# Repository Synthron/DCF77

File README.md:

# DCF77

DCF77-Clock with Multi-LED display with STM32

---

## Decription

This DCF77 Clock not only displays the time and date, but also analyzes and visualizes the signal received.  
The LED rings are placed as such that each LED is on its respective position on a standard clock face.  
The 7 Segment Displays show the time and date in a more readable format.

### Inner LED Ring

The inner LED ring clocks in the data for the current minute telegram. Each "1"-bit will be displayed by the LED lit up, on a "0", the LED is off respectively.

### Outer LED Ring

The outer LED ring gets updated after the current minute data is complete. On the "0-Second"-Mark, the data from the inner ring gets pushed to the outer ring and analyzed. The resulting data will then be displayed on the 7-Segment-Displays as well as the status LEDs. Also at each full hour, the internal RTC gets updated.

### RTC behaviour

1. Initial startup  
After the initial power-up the current RTC value will be pushed to the displays. This time information can only be trusted, once the module has received a valid telegram and was not powered down for more than 3 days.  
2. First received data  
Once the first valid data was received, it will be pushed into the RTC to update it. After successful write, the RTC_LOCK-LED will be on to indicate trustful data stored in the RTC.  
3. On the hour  
To mitigate possible clock drift, the RTC will be updated on the full hour. This ensures up-to-date data stored in it.

---

## Roadmap Hardware

- [x] finalize schematic
- [x] Set footprints
- [x] decide LED layout
  - all on one board
  - ~~seperate frontpanel pcb~~
- [x] Draw Layout
- [x] Review by theBrutzler
- [x] Order Parts
- [x] check footprints
- [x] Order PCB
- [x] Assemble

---

## Roadmap Software

- [ ] get USB running (for Debug)
- [x] Get DCF77 Antenna working and bits decoded
- [x] get MCP7221 running
- [x] get shift registers running
- [x] set up flags for stats and data
- [x] get LED rings running
- [x] get RTC running
- [x] Sync everything to start of minute/second
- [ ] get everything running together

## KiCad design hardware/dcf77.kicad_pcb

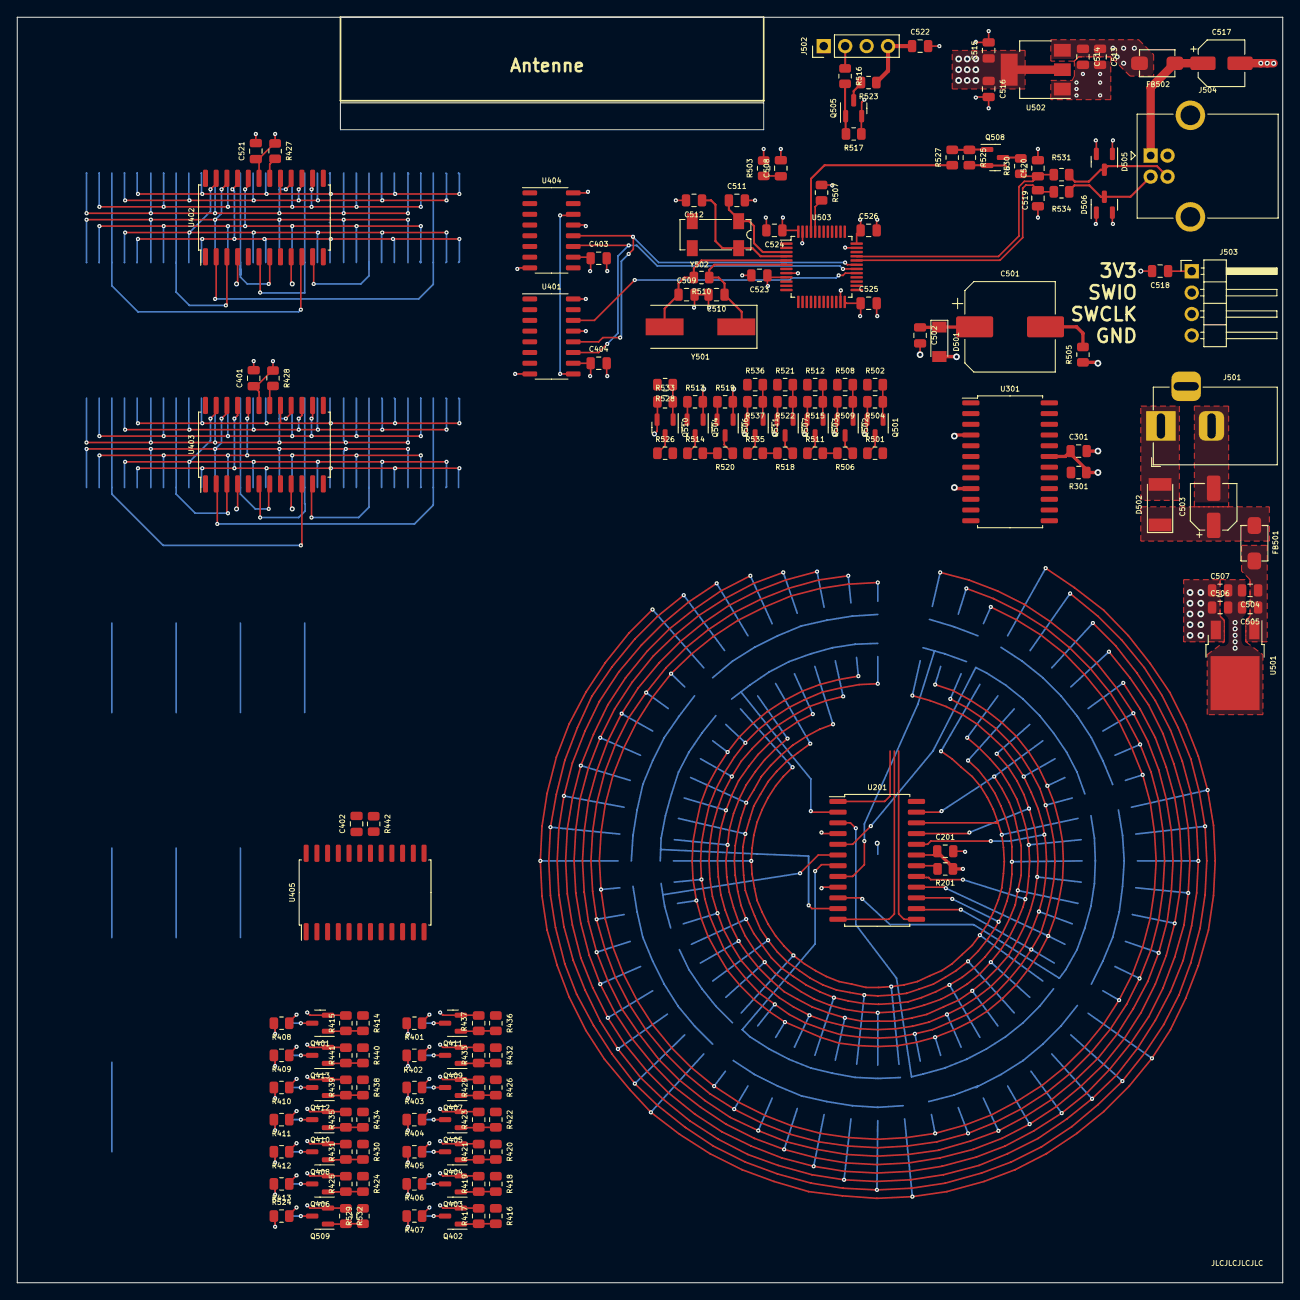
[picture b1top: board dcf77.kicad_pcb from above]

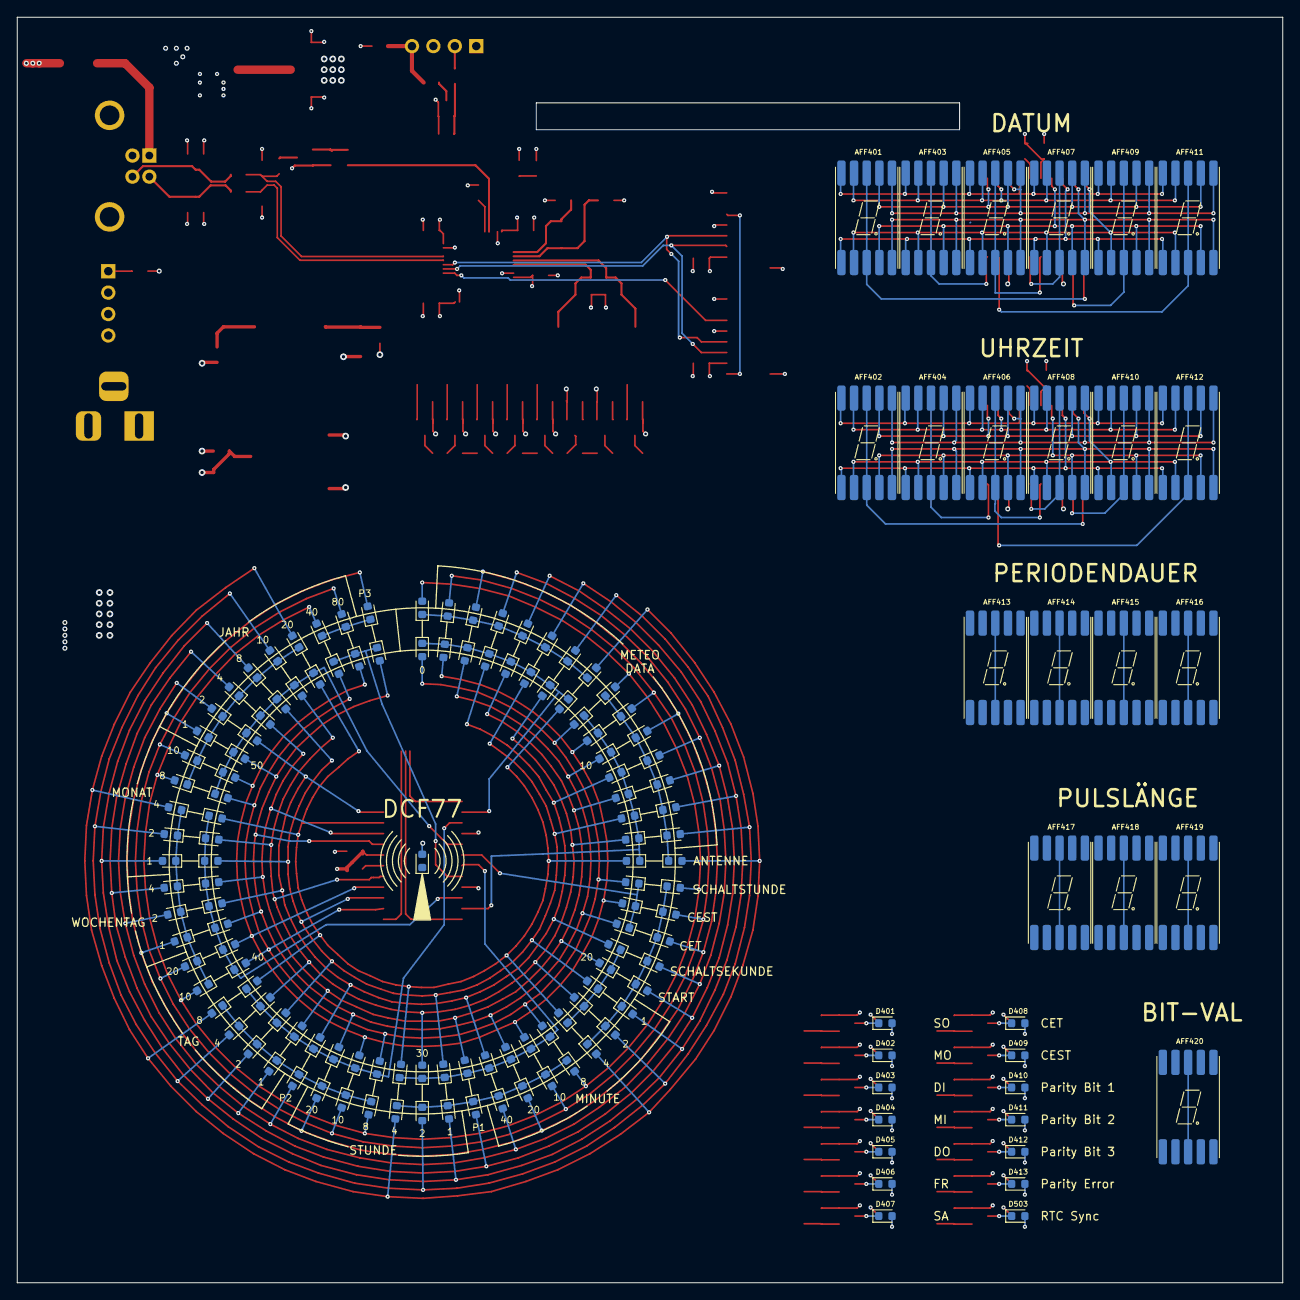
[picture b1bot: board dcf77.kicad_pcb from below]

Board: 4 copper layers, 150.0 x 150.0 mm, 312 parts (153 on the bottom side), 191 nets.

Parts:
AFF401, AFF402, AFF403, AFF404, AFF405, AFF406, AFF407, AFF408, AFF409, AFF410, AFF411, AFF412, AFF413, AFF414, AFF415, AFF416, AFF417, AFF418, AFF419, AFF420: LTS-6980HR; 7_Segment_SMD
C201, C301, C401, C402, C403, C404, C502, C505, C506, C508, C514, C515, C518, C521, C522, C523, C524, C525, C526: 100n; C_0805_2012Metric
C501: 0.22F/5V5; CP_Elec_10x10.5
C503: 100µ; CP_Elec_5x5.8
C504, C507, C513, C516: 1µ; C_0805_2012Metric
C509, C510, C511, C512: 20p; C_0805_2012Metric
C517: 10µ; CP_Elec_5x5.8
C519, C520: 47p; C_0805_2012Metric
D201, D202, D203, D204, D205, D206, D207, D208, D209, D210, D211, D212, D213, D214, D215, D216, D217, D218, D219, D220, D221, D222, D223, D224, D225, D226, D227, D228, D229, D230, D231, D232, D233, D234, D235, D236, D237, D238, D239, D240, D241, D242, D243, D244, D245, D246, D247, D248, D249, D250, D251, D252, D253, D254, D255, D256, D257, D258, D259, D301, D302, D303, D304, D305, D306, D307, D308, D309, D310, D311, D312, D313, D314, D315, D316, D317, D318, D319, D320, D321, D322, D323, D324, D325, D326, D327, D328, D329, D330, D331, D332, D333, D334, D335, D336, D337, D338, D339, D340, D341, D342, D343, D344, D345, D346, D347, D348, D349, D350, D351, D352, D353, D354, D355, D356, D357, D358, D359: LED; LED_0603_1608Metric
D401: Mo; LED_0603_1608Metric
D402: Di; LED_0603_1608Metric
D403: Mi; LED_0603_1608Metric
D404: Do; LED_0603_1608Metric
D405: Fr; LED_0603_1608Metric
D406: Sa; LED_0603_1608Metric
D407: So; LED_0603_1608Metric
D408: CET; LED_0603_1608Metric
D409: CEST; LED_0603_1608Metric
D410: P1; LED_0603_1608Metric
D411: P2; LED_0603_1608Metric
D412: P3; LED_0603_1608Metric
D413: PE; LED_0603_1608Metric
D501: LL4148; D_MiniMELF
D502: SM4007; D_MELF
D503: RTC; LED_0603_1608Metric
D504: SIG; LED_0603_1608Metric
D505, D506: BAV199; SOT-23
FB501, FB502: FerriteBead; SMB-001
J501: Jack-DC; BarrelJack_Horizontal
J502: DCF77 Antenna; PinHeader_1x04_P2.54mm_Vertical
J503: SWD; PinHeader_1x04_P2.54mm_Horizontal
J504: USB_B; USB_B_OST_USB-B1HSxx_Horizontal
Q401, Q402, Q403, Q404, Q405, Q406, Q407, Q408, Q409, Q410, Q411, Q412, Q413, Q501, Q502, Q503, Q504, Q505, Q506, Q507, Q509, Q510, Q511: BSS138; SOT-23
Q508: BC856; SOT-23
R201, R301, R427, R428, R442: 20k; R_0805_2012Metric
R401, R402, R403, R404, R405, R406, R407, R408, R409, R410, R411, R412, R413: R; R_0805_2012Metric
R414, R416, R418, R420, R422, R424, R426, R430, R432, R434, R436, R438, R440, R501, R502, R503, R505, R506, R507, R508, R511, R512, R513, R514, R516, R518, R519, R520, R521, R523, R528, R529, R535, R536: 10k; R_0805_2012Metric
R415, R417, R419, R421, R423, R425, R429, R431, R433, R435, R437, R439, R441, R504, R509, R515, R517, R522, R525, R527, R532, R533, R537: 100k; R_0805_2012Metric
R510: 1M; R_0805_2012Metric
R524, R526: 1k; R_0805_2012Metric
R530: 1k5; R_0805_2012Metric
R531, R534: 22; R_0805_2012Metric
U201, U301, U402, U403, U405: MAX7221xWG; SOIC-24W_7.5x15.4mm_P1.27mm
U401, U404: 74HC595; SO-16_3.9x9.9mm_P1.27mm
U501: L7805; TO-252-2
U502: AZ1117-3.3; SOT-223-3_TabPin2
U503: STM32F103C8Tx; LQFP-48_7x7mm_P0.5mm
Y501: 8MHz; Crystal_SMD_HC49-SD
Y502: 32.768kHz; Crystal_SMD_SeikoEpson_MC306-4Pin_8.0x3.2mm

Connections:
+3V3: C403.1, C404.1, C515.1, C516.1, C518.1, C522.1, C523.1, C524.1, C525.1, C526.1, D501.2 (A), D505.2, D506.2, J502.4, J503.1, Q504.1 (G), Q506.1 (G), Q508.2 (E), R503.2, R513.2, R519.2, R523.1, R525.2, U401.10 (~SRCLR), U401.16 (VCC), U404.10 (~SRCLR), U404.16 (VCC), U502.2 (VO), U503.9 (VDDA), U503.24 (VDD), U503.36 (VDD), U503.48 (VDD)
+5V: C201.1, C301.1, C401.1, C402.1, C506.1, C507.1, C513.1, C514.1, C521.1, D504.2 (A), FB502.2, R201.1, R301.1, R401.1, R402.1, R403.1, R404.1, R405.1, R406.1, R407.1, R408.1, R409.1, R410.1, R411.1, R412.1, R413.1, R427.1, R428.1, R442.1, R501.2, R506.2, R511.2, R514.2, R518.2, R520.2, R524.2, R535.2, U201.19 (V+), U301.19 (V+), U402.19 (V+), U403.19 (V+), U405.19 (V+), U501.3 (OUT), U502.3 (VI)
/CPU/CLK: Q504.3 (D), R514.1, U201.13 (CLK), U301.13 (CLK), U402.13 (CLK), U403.13 (CLK), U405.13 (CLK)
/CPU/MOSI: Q506.3 (D), R520.1, U201.1 (DIN), U301.1 (DIN), U402.1 (DIN), U403.1 (DIN), U405.1 (DIN)
/CPU/SER_CLK: U401.11 (SRCLK), U404.11 (SRCLK), U503.30 (PA9)
/CPU/SER_Data: U401.14 (SER), U503.29 (PA8)
/CPU/SER_Latch: U401.12 (RCLK), U404.12 (RCLK), U503.31 (PA10)
GND: C201.2, C301.2, C401.2, C402.2, C403.2, C404.2, C502.2, C503.2, C504.2, C505.2, C506.2, C507.2, C508.2, C509.2, C510.2, C511.2, C512.2, C513.2, C514.2, C515.2, C516.2, C517.2, C518.2, C519.2, C520.2, C521.2, C522.2, C523.2, C524.2, C525.2, C526.2, D505.1, D506.1, J501.2, J502.3, J503.4, J504.4 (GND), J504.5 (Shield), Q401.2 (S), Q402.2 (S), Q403.2 (S), Q404.2 (S), Q405.2 (S), Q406.2 (S), Q407.2 (S), Q408.2 (S), Q409.2 (S), Q410.2 (S), Q411.2 (S), Q412.2 (S), Q413.2 (S), Q501.2 (S), Q502.2 (S), Q503.2 (S), Q505.2 (S), Q507.2 (S), Q509.2 (S), Q510.2 (S), Q511.2 (S), R415.2, R417.2, R419.2, R421.2, R423.2, R425.2, R429.2, R431.2, R433.2, R435.2, R437.2, R439.2, R441.2, R504.2, R505.1, R507.1, R509.2, R515.2, R517.1, R522.2, R532.1, R533.1, R537.2, U201.4 (GND), U201.9 (GND), U301.4 (GND), U301.9 (GND), U401.8 (GND), U401.13 (~OE), U402.4 (GND), U402.9 (GND), U403.4 (GND), U403.9 (GND), U404.8 (GND), U404.13 (~OE), U405.4 (GND), U405.9 (GND), U501.2 (GND), U502.1 (GND), U503.8 (VSSA), U503.23 (VSS), U503.35 (VSS), U503.47 (VSS)
unnamed: AFF401.1 (e), AFF403.1 (e), AFF405.1 (e), AFF407.1 (e), AFF409.1 (e), AFF411.1 (e), U402.21 (SEG_E)
unnamed: AFF401.2 (d), AFF403.2 (d), AFF405.2 (d), AFF407.2 (d), AFF409.2 (d), AFF411.2 (d), U402.23 (SEG_D)
unnamed: AFF401.3 (C.K.), AFF401.8 (C.K.), U402.2 (DIG_0)
unnamed: AFF401.4 (c), AFF403.4 (c), AFF405.4 (c), AFF407.4 (c), AFF409.4 (c), AFF411.4 (c), U402.20 (SEG_C)
unnamed: AFF401.5 (DP), AFF403.5 (DP), AFF405.5 (DP), AFF407.5 (DP), AFF409.5 (DP), AFF411.5 (DP), U402.22 (SEG_DP)
unnamed: AFF401.6 (b), AFF403.6 (b), AFF405.6 (b), AFF407.6 (b), AFF409.6 (b), AFF411.6 (b), U402.16 (SEG_B)
unnamed: AFF401.7 (a), AFF403.7 (a), AFF405.7 (a), AFF407.7 (a), AFF409.7 (a), AFF411.7 (a), U402.14 (SEG_A)
unnamed: AFF401.9 (f), AFF403.9 (f), AFF405.9 (f), AFF407.9 (f), AFF409.9 (f), AFF411.9 (f), U402.15 (SEG_F)
unnamed: AFF401.10 (g), AFF403.10 (g), AFF405.10 (g), AFF407.10 (g), AFF409.10 (g), AFF411.10 (g), U402.17 (SEG_G)
unnamed: AFF402.1 (e), AFF404.1 (e), AFF406.1 (e), AFF408.1 (e), AFF410.1 (e), AFF412.1 (e), U403.21 (SEG_E)
unnamed: AFF402.2 (d), AFF404.2 (d), AFF406.2 (d), AFF408.2 (d), AFF410.2 (d), AFF412.2 (d), U403.23 (SEG_D)
unnamed: AFF402.3 (C.K.), AFF402.8 (C.K.), U403.2 (DIG_0)
unnamed: AFF402.4 (c), AFF404.4 (c), AFF406.4 (c), AFF408.4 (c), AFF410.4 (c), AFF412.4 (c), U403.20 (SEG_C)
unnamed: AFF402.5 (DP), AFF404.5 (DP), AFF406.5 (DP), AFF408.5 (DP), AFF410.5 (DP), AFF412.5 (DP), U403.22 (SEG_DP)
unnamed: AFF402.6 (b), AFF404.6 (b), AFF406.6 (b), AFF408.6 (b), AFF410.6 (b), AFF412.6 (b), U403.16 (SEG_B)
unnamed: AFF402.7 (a), AFF404.7 (a), AFF406.7 (a), AFF408.7 (a), AFF410.7 (a), AFF412.7 (a), U403.14 (SEG_A)
unnamed: AFF402.9 (f), AFF404.9 (f), AFF406.9 (f), AFF408.9 (f), AFF410.9 (f), AFF412.9 (f), U403.15 (SEG_F)
unnamed: AFF402.10 (g), AFF404.10 (g), AFF406.10 (g), AFF408.10 (g), AFF410.10 (g), AFF412.10 (g), U403.17 (SEG_G)
unnamed: AFF403.3 (C.K.), AFF403.8 (C.K.), U402.11 (DIG_1)
unnamed: AFF404.3 (C.K.), AFF404.8 (C.K.), U403.11 (DIG_1)
unnamed: AFF405.3 (C.K.), AFF405.8 (C.K.), U402.6 (DIG_2)
unnamed: AFF406.3 (C.K.), AFF406.8 (C.K.), U403.6 (DIG_2)
unnamed: AFF407.3 (C.K.), AFF407.8 (C.K.), U402.7 (DIG_3)
unnamed: AFF408.3 (C.K.), AFF408.8 (C.K.), U403.7 (DIG_3)
unnamed: AFF409.3 (C.K.), AFF409.8 (C.K.), U402.3 (DIG_4)
unnamed: AFF410.3 (C.K.), AFF410.8 (C.K.), U403.3 (DIG_4)
unnamed: AFF411.3 (C.K.), AFF411.8 (C.K.), U402.10 (DIG_5)
unnamed: AFF412.3 (C.K.), AFF412.8 (C.K.), U403.10 (DIG_5)
unnamed: AFF413.3 (C.K.), AFF413.8 (C.K.), U405.2 (DIG_0)
unnamed: AFF413.5 (DP), AFF414.5 (DP), AFF415.5 (DP), U405.22 (SEG_DP)
unnamed: AFF414.3 (C.K.), AFF414.8 (C.K.), U405.11 (DIG_1)
unnamed: AFF415.1 (e), AFF416.1 (e), AFF417.1 (e), AFF418.1 (e), AFF419.1 (e), AFF420.1 (e), U405.21 (SEG_E)
unnamed: AFF415.2 (d), AFF416.2 (d), AFF417.2 (d), AFF418.2 (d), AFF419.2 (d), AFF420.2 (d), U405.23 (SEG_D)
unnamed: AFF415.3 (C.K.), AFF415.8 (C.K.), U405.6 (DIG_2)
unnamed: AFF415.4 (c), AFF416.4 (c), AFF417.4 (c), AFF418.4 (c), AFF419.4 (c), AFF420.4 (c), U405.20 (SEG_C)
unnamed: AFF415.6 (b), AFF416.6 (b), AFF417.6 (b), AFF418.6 (b), AFF419.6 (b), AFF420.6 (b), U405.16 (SEG_B)
unnamed: AFF415.7 (a), AFF416.7 (a), AFF417.7 (a), AFF418.7 (a), AFF419.7 (a), AFF420.7 (a), U405.14 (SEG_A)
unnamed: AFF415.9 (f), AFF416.9 (f), AFF417.9 (f), AFF418.9 (f), AFF419.9 (f), AFF420.9 (f), U405.15 (SEG_F)
unnamed: AFF415.10 (g), AFF416.10 (g), AFF417.10 (g), AFF418.10 (g), AFF419.10 (g), AFF420.10 (g), U405.17 (SEG_G)
unnamed: AFF416.3 (C.K.), AFF416.8 (C.K.), U405.7 (DIG_3)
unnamed: AFF417.3 (C.K.), AFF417.8 (C.K.), U405.3 (DIG_4)
unnamed: AFF418.3 (C.K.), AFF418.8 (C.K.), U405.10 (DIG_5)
unnamed: AFF419.3 (C.K.), AFF419.8 (C.K.), U405.5 (DIG_6)
unnamed: AFF420.3 (C.K.), AFF420.8 (C.K.), U405.8 (DIG_7)
unnamed: C501.1, C502.1, D501.1 (K), U503.1 (VBAT)
unnamed: C501.2, R505.2
unnamed: C503.1, D502.1 (K), FB501.1
unnamed: C508.1, R503.1, U503.7 (NRST)
unnamed: C509.1, R510.2, U503.5 (PD0), Y501.2
unnamed: C510.1, R510.1, U503.6 (PD1), Y501.1
unnamed: C511.1, U503.3 (PC14), Y502.1
unnamed: C512.1, U503.4 (PC15), Y502.4
unnamed: C517.1, FB502.1, J504.1 (VBUS)
unnamed: D201.1 (K), D202.1 (K), D203.1 (K), D204.1 (K), D205.1 (K), D206.1 (K), D207.1 (K), D208.1 (K), U201.2 (DIG_0)
unnamed: D201.2 (A), D209.2 (A), D217.2 (A), D225.2 (A), D233.2 (A), D241.2 (A), D249.2 (A), D257.2 (A), U201.14 (SEG_A)
unnamed: D202.2 (A), D210.2 (A), D218.2 (A), D226.2 (A), D234.2 (A), D242.2 (A), D250.2 (A), D258.2 (A), U201.16 (SEG_B)
unnamed: D203.2 (A), D211.2 (A), D219.2 (A), D227.2 (A), D235.2 (A), D243.2 (A), D251.2 (A), D259.2 (A), U201.20 (SEG_C)
unnamed: D204.2 (A), D212.2 (A), D220.2 (A), D228.2 (A), D236.2 (A), D244.2 (A), D252.2 (A), U201.23 (SEG_D)
unnamed: D205.2 (A), D213.2 (A), D221.2 (A), D229.2 (A), D237.2 (A), D245.2 (A), D253.2 (A), U201.21 (SEG_E)
unnamed: D206.2 (A), D214.2 (A), D222.2 (A), D230.2 (A), D238.2 (A), D246.2 (A), D254.2 (A), U201.15 (SEG_F)
unnamed: D207.2 (A), D215.2 (A), D223.2 (A), D231.2 (A), D239.2 (A), D247.2 (A), D255.2 (A), U201.17 (SEG_G)
unnamed: D208.2 (A), D216.2 (A), D224.2 (A), D232.2 (A), D240.2 (A), D248.2 (A), D256.2 (A), U201.22 (SEG_DP)
unnamed: D209.1 (K), D210.1 (K), D211.1 (K), D212.1 (K), D213.1 (K), D214.1 (K), D215.1 (K), D216.1 (K), U201.11 (DIG_1)
unnamed: D217.1 (K), D218.1 (K), D219.1 (K), D220.1 (K), D221.1 (K), D222.1 (K), D223.1 (K), D224.1 (K), U201.6 (DIG_2)
unnamed: D225.1 (K), D226.1 (K), D227.1 (K), D228.1 (K), D229.1 (K), D230.1 (K), D231.1 (K), D232.1 (K), U201.7 (DIG_3)
unnamed: D233.1 (K), D234.1 (K), D235.1 (K), D236.1 (K), D237.1 (K), D238.1 (K), D239.1 (K), D240.1 (K), U201.3 (DIG_4)
unnamed: D241.1 (K), D242.1 (K), D243.1 (K), D244.1 (K), D245.1 (K), D246.1 (K), D247.1 (K), D248.1 (K), U201.10 (DIG_5)
unnamed: D249.1 (K), D250.1 (K), D251.1 (K), D252.1 (K), D253.1 (K), D254.1 (K), D255.1 (K), D256.1 (K), U201.5 (DIG_6)
unnamed: D257.1 (K), D258.1 (K), D259.1 (K), U201.8 (DIG_7)
unnamed: D301.1 (K), D302.1 (K), D303.1 (K), D304.1 (K), D305.1 (K), D306.1 (K), D307.1 (K), D308.1 (K), U301.2 (DIG_0)
unnamed: D301.2 (A), D309.2 (A), D317.2 (A), D325.2 (A), D333.2 (A), D341.2 (A), D349.2 (A), D357.2 (A), U301.14 (SEG_A)
unnamed: D302.2 (A), D310.2 (A), D318.2 (A), D326.2 (A), D334.2 (A), D342.2 (A), D350.2 (A), D358.2 (A), U301.16 (SEG_B)
unnamed: D303.2 (A), D311.2 (A), D319.2 (A), D327.2 (A), D335.2 (A), D343.2 (A), D351.2 (A), D359.2 (A), U301.20 (SEG_C)
unnamed: D304.2 (A), D312.2 (A), D320.2 (A), D328.2 (A), D336.2 (A), D344.2 (A), D352.2 (A), U301.23 (SEG_D)
unnamed: D305.2 (A), D313.2 (A), D321.2 (A), D329.2 (A), D337.2 (A), D345.2 (A), D353.2 (A), U301.21 (SEG_E)
unnamed: D306.2 (A), D314.2 (A), D322.2 (A), D330.2 (A), D338.2 (A), D346.2 (A), D354.2 (A), U301.15 (SEG_F)
unnamed: D307.2 (A), D315.2 (A), D323.2 (A), D331.2 (A), D339.2 (A), D347.2 (A), D355.2 (A), U301.17 (SEG_G)
unnamed: D308.2 (A), D316.2 (A), D324.2 (A), D332.2 (A), D340.2 (A), D348.2 (A), D356.2 (A), U301.22 (SEG_DP)
unnamed: D309.1 (K), D310.1 (K), D311.1 (K), D312.1 (K), D313.1 (K), D314.1 (K), D315.1 (K), D316.1 (K), U301.11 (DIG_1)
unnamed: D317.1 (K), D318.1 (K), D319.1 (K), D320.1 (K), D321.1 (K), D322.1 (K), D323.1 (K), D324.1 (K), U301.6 (DIG_2)
unnamed: D325.1 (K), D326.1 (K), D327.1 (K), D328.1 (K), D329.1 (K), D330.1 (K), D331.1 (K), D332.1 (K), U301.7 (DIG_3)
unnamed: D333.1 (K), D334.1 (K), D335.1 (K), D336.1 (K), D337.1 (K), D338.1 (K), D339.1 (K), D340.1 (K), U301.3 (DIG_4)
unnamed: D341.1 (K), D342.1 (K), D343.1 (K), D344.1 (K), D345.1 (K), D346.1 (K), D347.1 (K), D348.1 (K), U301.10 (DIG_5)
unnamed: D349.1 (K), D350.1 (K), D351.1 (K), D352.1 (K), D353.1 (K), D354.1 (K), D355.1 (K), D356.1 (K), U301.5 (DIG_6)
unnamed: D357.1 (K), D358.1 (K), D359.1 (K), U301.8 (DIG_7)
unnamed: D401.1 (K), Q411.3 (D)
unnamed: D401.2 (A), R401.2
unnamed: D402.1 (K), Q409.3 (D)
unnamed: D402.2 (A), R402.2
unnamed: D403.1 (K), Q407.3 (D)
unnamed: D403.2 (A), R403.2
unnamed: D404.1 (K), Q405.3 (D)
unnamed: D404.2 (A), R404.2
unnamed: D405.1 (K), Q404.3 (D)
unnamed: D405.2 (A), R405.2
unnamed: D406.1 (K), Q403.3 (D)
unnamed: D406.2 (A), R406.2
unnamed: D407.1 (K), Q402.3 (D)
unnamed: D407.2 (A), R407.2
unnamed: D408.1 (K), Q401.3 (D)
unnamed: D408.2 (A), R408.2
unnamed: D409.1 (K), Q413.3 (D)
unnamed: D409.2 (A), R409.2
unnamed: D410.1 (K), Q412.3 (D)
unnamed: D410.2 (A), R410.2
unnamed: D411.1 (K), Q410.3 (D)
unnamed: D411.2 (A), R411.2
unnamed: D412.1 (K), Q408.3 (D)
unnamed: D412.2 (A), R412.2
unnamed: D413.1 (K), Q406.3 (D)
unnamed: D413.2 (A), R413.2
unnamed: D502.2 (A), J501.1
unnamed: D503.1 (K), Q509.3 (D)
unnamed: D503.2 (A), R524.1
unnamed: D505.3, J504.3 (D+), R531.1
unnamed: D506.3, J504.2 (D-), R534.1
unnamed: J502.1, U503.27 (PB14)
unnamed: J502.2, R516.1
unnamed: Q401.1 (G), R414.2, R415.1
unnamed: Q402.1 (G), R416.2, R417.1
unnamed: Q403.1 (G), R418.2, R419.1
unnamed: Q404.1 (G), R420.2, R421.1
unnamed: Q405.1 (G), R422.2, R423.1
unnamed: Q406.1 (G), R424.2, R425.1
unnamed: Q407.1 (G), R426.2, R429.1
unnamed: Q408.1 (G), R430.2, R431.1
unnamed: Q409.1 (G), R432.2, R433.1
unnamed: Q410.1 (G), R434.2, R435.1
unnamed: Q411.1 (G), R436.2, R437.1
unnamed: Q412.1 (G), R438.2, R439.1
unnamed: Q413.1 (G), R440.2, R441.1
unnamed: Q501.1 (G), R502.2, R504.1
unnamed: Q501.3 (D), R501.1
unnamed: Q502.1 (G), R508.2, R509.1
unnamed: Q502.3 (D), R506.1
unnamed: Q503.1 (G), R512.2, R515.1
unnamed: Q503.3 (D), R511.1
unnamed: Q504.2 (S), R513.1, U503.15 (PA5)
unnamed: Q505.1 (G), R516.2, R517.2
unnamed: Q505.3 (D), R523.2, R528.2, U503.28 (PB15)
unnamed: Q506.2 (S), R519.1, U503.17 (PA7)
unnamed: Q507.1 (G), R521.2, R522.1
unnamed: Q507.3 (D), R518.1
unnamed: Q508.1 (B), R525.1, R527.2
unnamed: Q508.3 (C), R530.2
unnamed: Q509.1 (G), R529.1, R532.2
unnamed: Q510.1 (G), R528.1, R533.2
unnamed: Q511.1 (G), R536.2, R537.1
unnamed: Q511.3 (D), R535.1
unnamed: R201.2, U201.18 (ISET)
unnamed: R301.2, U301.18 (ISET)
unnamed: R414.1, U401.15 (QA)
unnamed: R416.1, U401.1 (QB)
unnamed: R418.1, U401.2 (QC)
unnamed: R420.1, U401.3 (QD)
unnamed: R422.1, U401.4 (QE)
unnamed: R424.1, U404.15 (QA)
unnamed: R426.1, U401.5 (QF)
unnamed: R427.2, U402.18 (ISET)
unnamed: R428.2, U403.18 (ISET)
unnamed: R430.1, U404.1 (QB)
unnamed: R432.1, U401.6 (QG)
unnamed: R434.1, U404.2 (QC)
unnamed: R436.1, U401.7 (QH)
unnamed: R438.1, U404.3 (QD)
unnamed: R440.1, U404.4 (QE)
unnamed: R442.2, U405.18 (ISET)
unnamed: R502.1, U503.10 (PA0)
unnamed: R507.2, U503.44 (BOOT0)
unnamed: R508.1, U503.11 (PA1)
unnamed: R512.1, U503.12 (PA2)
unnamed: R521.1, U503.13 (PA3)
unnamed: Q510.3 (D), R526.1
unnamed: D504.1 (K), R526.2
unnamed: R529.2, U503.38 (PA15)
unnamed: R536.1, U503.14 (PA4)
unnamed: U401.9 (QH'), U404.14 (SER)
SWCLK: J503.3, U503.37 (PA14)
SWIO: J503.2, U503.34 (PA13)
USB+: C520.1, R530.1, R531.2, U503.33 (PA12)
USB-: C519.1, R534.2, U503.32 (PA11)
VBUS: C504.1, C505.1, FB501.2, U501.1 (IN)
/Disconnect: R527.1, U503.45 (PB8)

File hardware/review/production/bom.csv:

Designator,Footprint,Quantity,Value,LCSC Part #
"AFF401, AFF402, AFF403, AFF404, AFF405, AFF406, AFF407, AFF408, AFF409, AFF410, AFF411, AFF412, AFF413, AFF414, AFF415, AFF416, AFF417, AFF418, AFF419, AFF420",7_Segment_SMD,20,LTS-6980HR,
C1,C_0805_2012Metric,1,4µ7,
"C201, C301, C401, C402, C403, C404, C502, C505, C506, C508, C514, C515, C518, C521, C522, C523, C524, C525, C526",C_0805_2012Metric,19,100n,
C501,CP_Elec_10x10.5,1,0.22F/5V5,
C503,CP_Elec_5x5.8,1,100µ,
"C504, C507, C513, C516",C_0805_2012Metric,4,1µ,
"C509, C510, C511, C512",C_0805_2012Metric,4,20p,
C517,CP_Elec_5x5.8,1,10µ,
"C519, C520",C_0805_2012Metric,2,47p,
"D201, D202, D203, D204, D205, D206, D207, D208, D209, D210, D211, D212, D213, D214, D215, D216, D217, D218, D219, D220, D221, D222, D223, D224, D225, D226, D227, D228, D229, D230, D231, D232, D233, D234, D235, D236, D237, D238, D239, D240, D241, D242, D243, D244, D245, D246, D247, D248, D249, D250, D251, D252, D253, D254, D255, D256, D257, D258, D259, D301, D302, D303, D304, D305, D306, D307, D308, D309, D310, D311, D312, D313, D314, D315, D316, D317, D318, D319, D320, D321, D322, D323, D324, D325, D326, D327, D328, D329, D330, D331, D332, D333, D334, D335, D336, D337, D338, D339, D340, D341, D342, D343, D344, D345, D346, D347, D348, D349, D350, D351, D352, D353, D354, D355, D356, D357, D358, D359",LED_0603_1608Metric,118,LED,
D401,LED_0603_1608Metric,1,Mo,
D402,LED_0603_1608Metric,1,Di,
D403,LED_0603_1608Metric,1,Mi,
D404,LED_0603_1608Metric,1,Do,
D405,LED_0603_1608Metric,1,Fr,
D406,LED_0603_1608Metric,1,Sa,
D407,LED_0603_1608Metric,1,So,
D408,LED_0603_1608Metric,1,CET,
D409,LED_0603_1608Metric,1,CEST,
D410,LED_0603_1608Metric,1,P1,
D411,LED_0603_1608Metric,1,P2,
D412,LED_0603_1608Metric,1,P3,
D413,LED_0603_1608Metric,1,PE,
D501,D_MiniMELF,1,LL4148,
D502,D_MELF,1,SM4007,
D503,LED_0603_1608Metric,1,RTC,
D504,LED_0603_1608Metric,1,SIG,
"D505, D506",SOT-23,2,BAV199,
"FB501, FB502",SMB-001,2,FerriteBead,
J501,BarrelJack_Horizontal,1,Jack-DC,
J502,PinHeader_1x04_P2.54mm_Vertical,1,DCF77 Antenna,
J503,PinHeader_1x04_P2.54mm_Horizontal,1,SWD,
J504,USB_B_OST_USB-B1HSxx_Horizontal,1,USB_B,
"Q401, Q402, Q403, Q404, Q405, Q406, Q407, Q408, Q409, Q410, Q411, Q412, Q413, Q501, Q502, Q503, Q504, Q505, Q506, Q507, Q509, Q510, Q511",SOT-23,23,BSS138,
Q508,SOT-23,1,BC856,
"R201, R301, R427, R428, R442",R_0805_2012Metric,5,20k,
"R401, R402, R403, R404, R405, R406, R407, R408, R409, R410, R411, R412, R413",R_0805_2012Metric,13,R,
"R414, R416, R418, R420, R422, R424, R426, R430, R432, R434, R436, R438, R440, R501, R502, R503, R506, R508, R511, R512, R513, R514, R516, R518, R519, R520, R521, R523, R528, R529, R535, R536",R_0805_2012Metric,32,10k,
"R415, R417, R419, R421, R423, R425, R429, R431, R433, R435, R437, R439, R441, R504, R509, R515, R517, R522, R525, R527, R532, R533, R537",R_0805_2012Metric,23,100k,
R505,R_0805_2012Metric,1,100,
"R507, R524, R526",R_0805_2012Metric,3,1k,
R510,R_0805_2012Metric,1,1M,
R530,R_0805_2012Metric,1,1k5,
"R531, R534",R_0805_2012Metric,2,22,
"U201, U301, U402, U403, U405",SOIC-24W_7.5x15.4mm_P1.27mm,5,MAX7221xWG,
"U401, U404",SO-16_3.9x9.9mm_P1.27mm,2,74HC595,
U501,TO-263-2,1,L7805,
U502,SOT-223-3_TabPin2,1,AZ1117-3.3,
U503,LQFP-48_7x7mm_P0.5mm,1,STM32F103C8Tx,
Y501,Crystal_SMD_HC49-SD,1,8MHz,
Y502,Crystal_SMD_SeikoEpson_MC306-4Pin_8.0x3.2mm,1,32.768kHz,

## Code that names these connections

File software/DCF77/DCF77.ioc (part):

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Mcu.Name=STM32F103C(8-B)Tx
Mcu.Package=LQFP48
Mcu.UserName=STM32F103C8Tx
PA0-WKUP.Signal=GPIO_Output
PA1.Signal=GPIO_Output
PA10.Signal=GPIO_Output
PA11.Mode=Device
PA11.Signal=USB_DM
PA12.Mode=Device
PA12.Signal=USB_DP
PA13.Mode=Serial_Wire
PA13.Signal=SYS_JTMS-SWDIO
PA14.Mode=Serial_Wire
PA14.Signal=SYS_JTCK-SWCLK
PA15.Signal=GPIO_Output
PA2.Signal=GPIO_Output
PA3.Signal=GPIO_Output
PA4.Signal=GPIO_Output
PA5.Mode=TX_Only_Simplex_Unidirect_Master
PA5.Signal=SPI1_SCK
PA7.Mode=TX_Only_Simplex_Unidirect_Master
PA7.Signal=SPI1_MOSI
PA8.Signal=GPIO_Output
PA9.Signal=GPIO_Output
PB14.Signal=GPIO_Output
PB15.Signal=GPXTI15
PB8.Signal=GPIO_Output
PC14-OSC32_IN.Mode=LSE-External-Oscillator
PC14-OSC32_IN.Signal=RCC_OSC32_IN
PC15-OSC32_OUT.Mode=LSE-External-Oscillator
PC15-OSC32_OUT.Signal=RCC_OSC32_OUT
PD0-OSC_IN.Mode=HSE-External-Oscillator
PD0-OSC_IN.Signal=RCC_OSC_IN
PD1-OSC_OUT.Mode=HSE-External-Oscillator
PD1-OSC_OUT.Signal=RCC_OSC_OUT
RCC.SYSCLKFreq_VALUE=72000000
RCC.SYSCLKSource=RCC_SYSCLKSOURCE_PLLCLK
board=custom

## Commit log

2022-09-26 start layout, finalize schematic
2022-09-26 update Layout
2022-09-27 update Schematic
2022-09-29 finalize initial routing
2022-10-01 finalize laoyut
2022-10-01 pretty up layout generate code structure
2022-10-03 code update
2022-10-05 Review
2022-10-07 finalize layout
2022-10-23 update resistor values in Schematic and BOM Bugfix in Code added test stand
